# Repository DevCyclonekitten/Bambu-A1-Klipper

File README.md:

# Bambu-A1-Klipper
 A repository about the development of modifying a bambu labs a1 printer to run on klipper

Site viewable at: https://devcyclonekitten.github.io/Bambu-A1-Klipper/

Uhh this hasn't been updated, but so far I did get the printer working, then killed mainboard
I have all components working, except screen and eddy current sensor, am just finalizing pcb's then trying to rebuild.

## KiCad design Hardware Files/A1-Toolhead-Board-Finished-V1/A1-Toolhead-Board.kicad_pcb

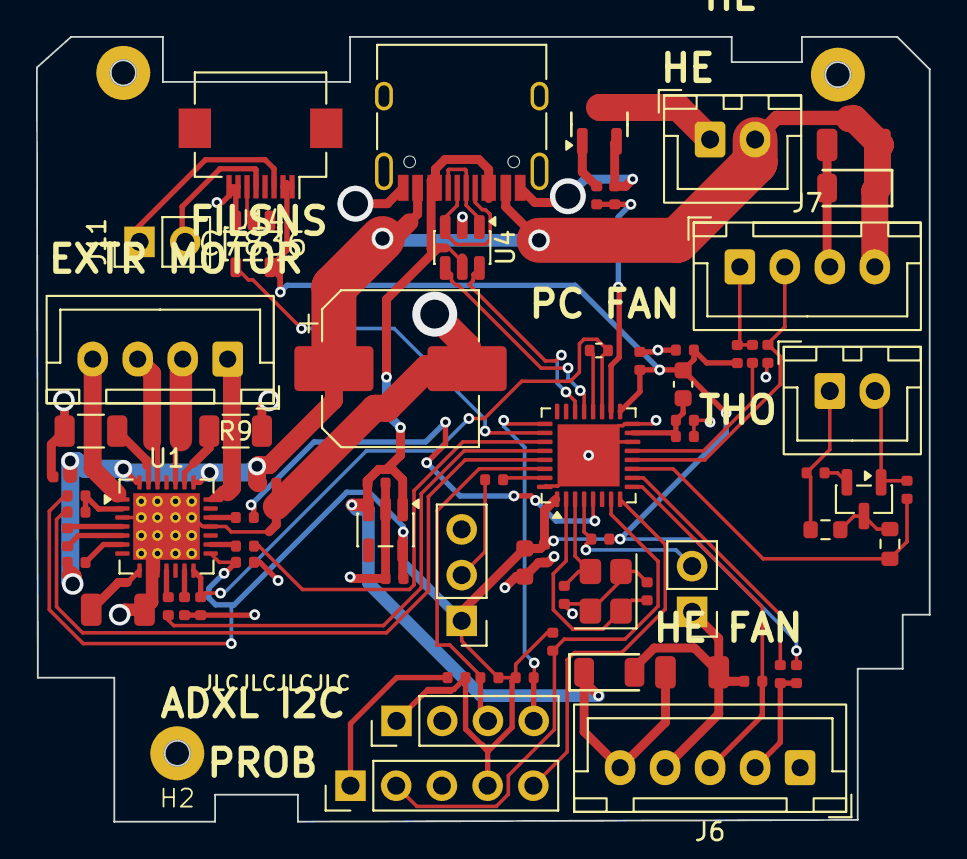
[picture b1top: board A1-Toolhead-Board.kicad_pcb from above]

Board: 2 copper layers, 49.6 x 43.6 mm, 74 parts (0 on the bottom side), 56 nets.

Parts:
C1, C3, C4, C5, C8, C13, C16: 100nF; C_0402
C2: 100uF 50V; CP_Elec_8x10.5
C6: 22nF; C_0402
C7, C11, C12: 4.7uF; C_1206
C9, C17, C18, C21, C24: 1uF; C_0402
C19: 10uF; C_0603
C20: 10nF; C_0402
C22, C23: 30pF; C_0402
D1, D4: DSK26; D_SOD-123FL
D3: BAV99; SOT-23
FB1: 120r 100MHz; C_0603_1608Metric
H1, H2, H3: m1.5; MountingHole_M1.5
J1: Motor_E; JST_XH_B4B-XH-A_1x04_P2.50mm_Vertical
J2: BOOT; PinHeader_1x03_P2.54mm_Vertical
J6: EXF; JST_XH_B5B-XH-A_1x05_P2.50mm_Vertical
J7: PCF; JST_XH_B4B-XH-A_1x04_P2.50mm_Vertical
J9: ADXL345; PinHeader_1x04_P2.54mm_Vertical
J10: BL_PROBE; PinHeader_1x05_P2.54mm_Vertical
J11: EXTR_FIL; PinHeader_1x02_P2.54mm_Vertical
J12: THO; JST_XH_B2B-XH-A_1x02_P2.50mm_Vertical
J13: HE; JST_XH_B2B-XH-A_1x02_P2.50mm_Vertical
J14: FPC_FILAMENT_SENSOR; Hirose_FH12-8S-0.5SH_1x08-1MP_P0.50mm_Horizontal
P1: USB_C_Plug; USB_C_Receptacle_HRO_TYPE-C-31-M-12
PN1: Part_Num_JLCPCB
Q2: AO3400A; Q_SOT-23
R1: 1ko; R_0402_1005Metric
R2, R5, R8: 20kΩ; R_0402
R3, R4, R6, R21: 100Ω; R_0402
R7, R11, R19, R20, R24, R25, R28, R30: 10kΩ; R_0402
R9, R100: 100mO; R_1206_3216Metric
R16, R23, R26, R29, R31: 4.7kΩ; R_0402
R17, R18: 2.2kΩ; R_0603_1608Metric
R27: 10Ω; R_0402
SW1: SW_SPST; PinHeader_1x02_P2.54mm_Vertical
U1: TMC2209-LA; TMC2209-LargerVias
U2: STM32G431KBU3; QFN-32-1EP_5x5mm_P0.5mm_EP3.45x3.45mm
U4: USBLC6-2SC6; SOT-23-6
U5: TLV75733PDBV; SOT-23-5
U6: 74LVC1G17; SOT-23-5_L3.0-W1.7-P0.95-LS2.8-BR
Y1: Crystal_GND24; Crystal_SMD_3225-4Pin_3.2x2.5mm

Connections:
+3.3VADC: D3.2 (A), R16.1
+3V3: C8.1, C9.2, C13.1, C16.1, C17.1, C19.1, C21.1, FB1.2, J2.1, J9.1, J10.4, J14.1, J14.2, R5.2, R11.1, R19.2, R24.2, R26.2, R28.1, R29.2, U1.15 (VCC_IO), U2.1 (VDD), U2.17 (VDD), U5.5 (OUT), U6.5 (VCC)
+3V3A: C18.1, C20.1, FB1.1, U2.15 (VDDA)
+5V: C7.1, U1.8 (5VOUT)
+24V: C2.1, C3.1, C4.1, C5.2, C12.1, D1.1, J7.4, J13.2, P1.A4 (VBUS), P1.A9 (VBUS), P1.B4 (VBUS), P1.B9 (VBUS), U1.22 (VS), U1.28 (VS)
/communications/USB_D+: U2.22 (PA12), U4.6 (I/O1)
/communications/USB_D-: U2.21 (PA11), U4.4 (I/O2)
/communications/USB_PORT_D+: P1.A6 (D+), P1.B6 (D+), U4.1 (I/O1)
/communications/USB_PORT_D-: P1.A7 (D-), P1.B7 (D-), U4.3 (I/O2)
/fans/EXTR_FAN_PWM: J6.3, R23.1, U2.9 (PA4)
/fans/EXTR_FAN_TACH: R20.1, U2.10 (PA5)
/fans/PART_FAN_PWM: J7.2, R31.1, U2.12 (PA7)
/fans/PART_FAN_TACH: R25.1, U2.13 (PB0)
/heaters/HOTEND_PWM: R27.2, R30.2, U2.18 (PA8)
/heaters/THERMISTER: C1.1, R17.1, U2.11 (PA6)
/mcu/ADXL_SCK: J9.4, R26.1, U2.25 (PA15)
/mcu/ADXL_SDA: J9.3, R29.1, U2.30 (PB7)
/mcu/BIQU_BL_PROBE: J10.2, R28.2, U2.7 (PA2)
/mcu/BIQU_BL_SERVO: J10.5, U2.8 (PA3)
/mcu/EXTRUDER_DIAG: R21.1, U2.28 (PB5)
/mcu/EXTRUDER_DIR: R6.1, U2.5 (PA0)
/mcu/EXTRUDER_ENABLE: R3.1, U2.29 (PB6)
/mcu/EXTRUDER_RX: R1.1, U2.20 (PA10)
/mcu/EXTRUDER_STEP: R4.2, U2.27 (PB4)
/mcu/EXTRUDER_TX: R1.2, R2.2, U1.14 (~PD_UART), U2.19 (PA9)
/mcu/FILAMENT_SENSOR: U2.26 (PB3), U6.4
/reversed_filament_sensor/SNS1: J11.1, J14.3
/reversed_filament_sensor/SNS2: J11.2, J14.5
/reversed_filament_sensor/SNS3: J14.6, U6.2
GND: C1.2, C2.2, C3.2, C4.2, C7.2, C8.2, C9.1, C11.2, C12.2, C13.2, C16.2, C17.2, C18.2, C19.2, C20.2, C21.2, C22.2, C23.2, C24.1, D1.2, D3.1 (K), D4.2, J2.3, J6.4, J7.3, J9.2, J10.1, J10.3, J12.2, J14.7, J14.8, P1.A1 (GND), P1.A12 (GND), P1.B1 (GND), P1.B12 (GND), Q2.2 (S), R2.1, R8.1, R9.2, R23.2, R30.1, R31.2, R100.2, SW1.1 (A), U1.3 (GND), U1.9 (MS1_AD0), U1.10 (MS2_AD1), U1.18 (GND), U1.29 (EXP), U2.14 (VSSA), U2.16 (VSS), U2.32 (VSS), U2.33 (VSS), U4.2 (GND), U5.2 (GND), U6.3 (GND), Y1.2, Y1.4
unnamed: D3.3 (K), R17.2, R18.1
unnamed: J1.1, U1.21 (OA2)
unnamed: J1.2, U1.24 (OA1)
unnamed: J1.3, U1.26 (OB1)
unnamed: J1.4, U1.1 (OB2)
unnamed: J2.2, R7.1
unnamed: J6.2, R19.1, R20.2
unnamed: J7.1, R24.1, R25.2
unnamed: J12.1, R16.2, R18.2
unnamed: J13.1, Q2.3 (D)
unnamed: Q2.1 (G), R27.1
unnamed: R11.2, SW1.2 (B), U2.4 (PG10)
unnamed: R9.1, U1.23 (BRA)
unnamed: R100.1, U1.27 (BRB)
unnamed: R8.2, U1.13 (CLK)
unnamed: C6.1, U1.5 (CPI)
unnamed: C6.2, U1.4 (CPO)
unnamed: R21.2, U1.11 (DIAG)
unnamed: R6.2, U1.19 (DIR)
unnamed: R4.1, U1.16 (STEP)
unnamed: C5.1, U1.6 (VCP)
unnamed: R3.2, R5.1, U1.2 (~EN)
unnamed: R7.2, U2.31 (PB8)
unnamed: C23.1, U2.2 (PF0), Y1.1
unnamed: C22.1, U2.3 (PF1), Y1.3
VBUS: C11.1, C24.2, D4.1, J6.5, P1.A5 (CC1), P1.A8 (SBU1), P1.B5 (CC2), P1.B8 (SBU2), U4.5 (VBUS), U5.1 (IN), U5.3 (EN)

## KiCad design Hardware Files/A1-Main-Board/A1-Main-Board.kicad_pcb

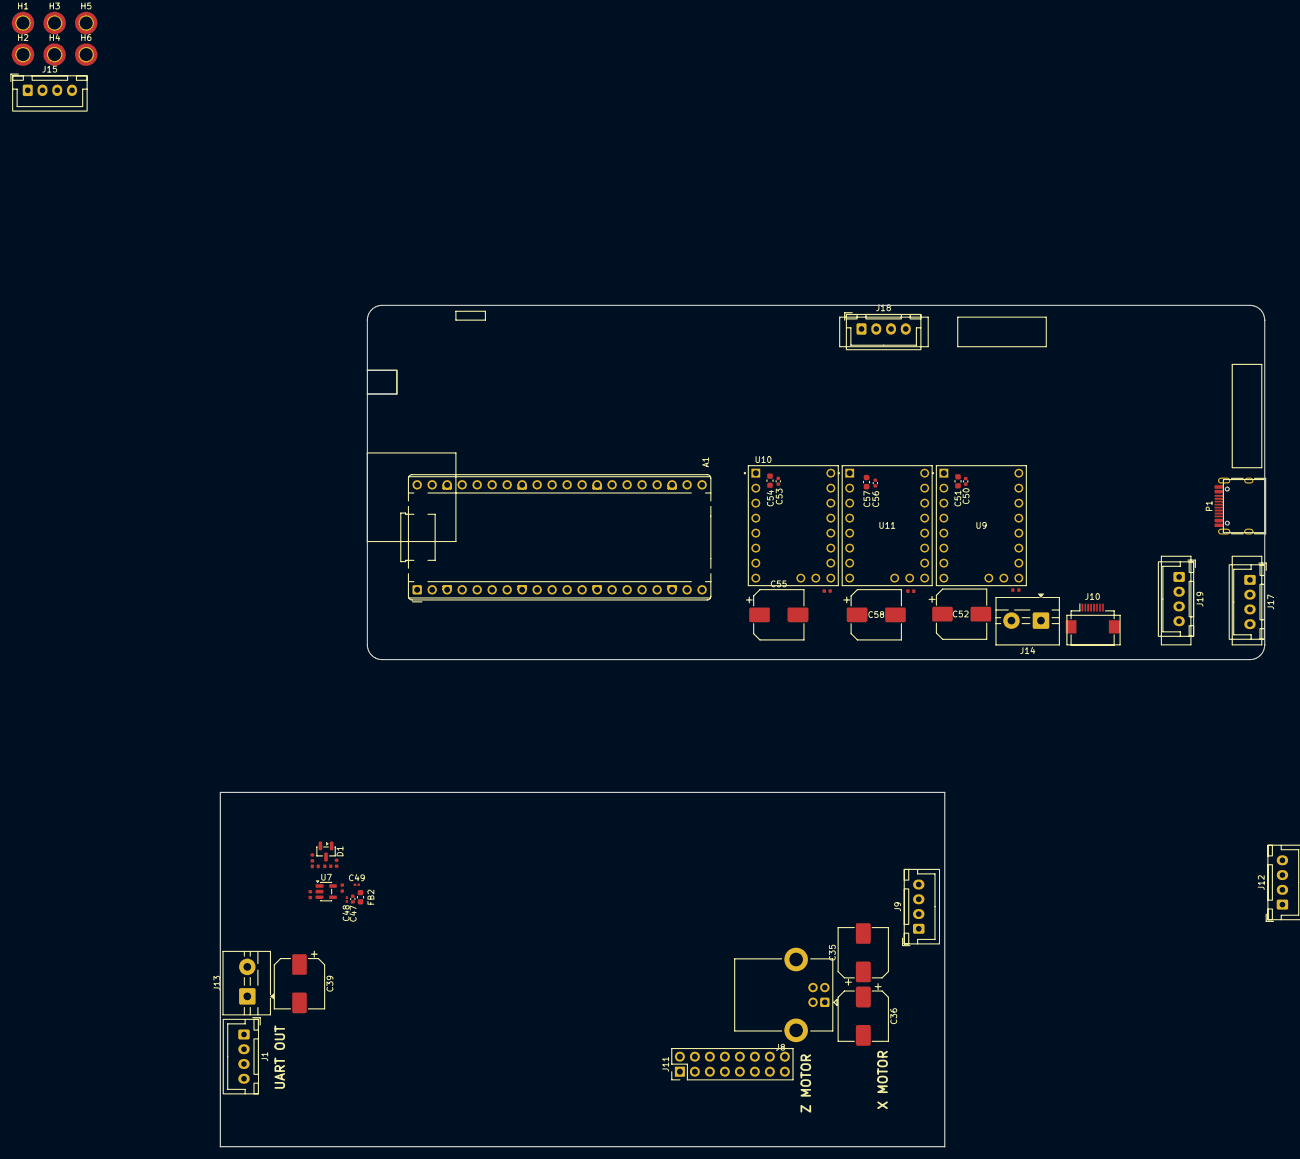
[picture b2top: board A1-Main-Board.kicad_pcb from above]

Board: 2 copper layers, 176.9 x 142.5 mm, 50 parts (0 on the bottom side), 38 nets, no tracks yet.

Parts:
A1: RaspberryPi_Pico; RaspberryPi_Pico_Common_THT
C35, C36, C39, C52, C55, C58: 100uF; CP_Elec_8x10
C42, C43: 1uF; C_0402
C47: 10nF; C_0402_1005Metric
C48, C49: 1uF; C_0201_0603Metric
C50, C53, C56: 100nF; C_0402_1005Metric
C51, C54, C57: 10uF; C_0603_1608Metric
C59: 100nF; C_0402
D1: BAV99; SOT-23
FB2: 120r 100MHz; C_0603_1608Metric
H1, H2, H3, H4, H5, H6: M1.5; MountingHole_2.2mm_M2_ISO14580_Pad_TopBottom
J1: MB_UART; JST_XH_B4B-XH-A_1x04_P2.50mm_Vertical
J8: USB_Toolhead_Outgoing; USB_B_Lumberg_2411_02_Horizontal
J9: Toolhead_USB; JST_XH_B4B-XH-A_1x04_P2.50mm_Vertical
J10: FPC_CON; Hirose_FH12-8S-0.5SH_1x08-1MP_P0.50mm_Horizontal
J11: Bed-Binder; PinHeader_2x08_P2.54mm_Vertical
J12: MotorJST; JST_XH_B4B-XH-A_1x04_P2.50mm_Vertical
J13, J14: Power-Input; TerminalBlock_MaiXu_MX126-5.0-02P_1x02_P5.00mm
J15: ExpansionPortJST; JST_XH_B4B-XH-A_1x04_P2.50mm_Vertical
J17, J18, J19: Motor Connector; JST_XH_B4B-XH-A_1x04_P2.50mm_Vertical
P1: USB_Toolhead_Incoming; USB_C_Receptacle_HRO_TYPE-C-31-M-12
R32, R33: 2.2kΩ; R_0402
R38, R39, R40: 10kΩ; R_0402
R41: 4.7kΩ; R_0402
U7: TLV75733PDBV; SOT-23-5
U9, U10, U11: TMC2209_SILENTSTEPSTICK; MODULE_TMC2209_SILENTSTEPSTICK

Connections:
+3V3: C43.1, C49.1, C50.1, C51.1, C53.1, C54.1, C56.1, C57.1, FB2.2, J1.4, R38.1, R39.1, R40.1, U7.5 (OUT), U9.2 (VIO), U10.2 (VIO), U10.15 (MS1), U11.2 (VIO)
+3V3A: A1.35 (ADC_VREF), C47.1, C48.1, D1.2 (A), FB2.1, R41.1
+5V: A1.39 (VSYS), C36.1, C39.1, J11.2, J13.2, P1.A5 (CC), P1.A8 (SBU1), P1.B5 (VCONN), P1.B8 (SBU2)
+24V: C35.1, C52.1, C55.1, C58.1, J14.2, P1.A4 (VBUS), P1.A9 (VBUS), P1.B4 (VBUS), P1.B9 (VBUS), U9.8 (VM), U10.8 (VM), U11.8 (VM)
/communications-toolhead/USB_D+: J8.3 (D+), J9.2, P1.A6 (D+)
/communications-toolhead/USB_D-: J8.2 (D-), J9.3, P1.A7 (D-)
/drivers/MA_DIAG: A1.7 (GPIO5), U9.18 (DIAG)
/drivers/MA_DIR: A1.6 (GPIO4), U9.9 (DIR)
/drivers/MA_ENABLE: A1.4 (GPIO2), R38.2, U9.16 (~EN)
/drivers/MA_STEP: A1.5 (GPIO3), U9.10 (STEP)
/drivers/MA_UART: A1.16 (GPIO12), U9.12 (UART), U10.12 (UART), U11.12 (UART)
/drivers/MB_DIAG: A1.12 (GPIO9), U10.18 (DIAG)
/drivers/MB_DIR: A1.11 (GPIO8), U10.9 (DIR)
/drivers/MB_ENABLE: A1.9 (GPIO6), R39.2, U10.16 (~EN)
/drivers/MB_STEP: A1.10 (GPIO7), U10.10 (STEP)
/drivers/MC_DIAG: A1.26 (GPIO20), U11.18 (DIAG)
/drivers/MC_DIR: A1.25 (GPIO19), U11.9 (DIR)
/drivers/MC_ENABLE: A1.22 (GPIO17), R40.2, U11.16 (~EN)
/drivers/MC_STEP: A1.24 (GPIO18), U11.10 (STEP)
/heated-bed/100k_THB_INP: J12.1, R33.1, R41.2
/heated-bed/BED_THERM_1: A1.31 (GPIO26_ADC0), C59.1, R32.2
/mcu-pico-tht/UART_RX: A1.2 (GPIO1), J1.2
/mcu-pico-tht/UART_TX: A1.1 (GPIO0), J1.3
GND: A1.3 (GND), A1.8 (GND), A1.13 (GND), A1.18 (GND), A1.23 (GND), A1.28 (GND), A1.33 (AGND), A1.38 (GND), C35.2, C36.2, C39.2, C42.1, C43.2, C47.2, C48.2, C49.2, C50.2, C51.2, C52.2, C53.2, C54.2, C55.2, C56.2, C57.2, C58.2, C59.2, D1.1 (K), J1.1, J8.4 (GND), J9.4, J11.6, J11.10, J11.14, J11.16, J12.2, J13.1, J14.1, P1.A1 (GND), P1.A12 (GND), P1.B1 (GND), P1.B12 (GND), U7.2 (GND), U9.1 (GND), U9.7 (GND), U9.14 (MS2), U9.15 (MS1), U10.1 (GND), U10.7 (GND), U10.14 (MS2), U11.1 (GND), U11.7 (GND), U11.15 (MS1)
unnamed: D1.3 (K), R32.1, R33.2
unnamed: J17.1, U9.5 (M2A)
unnamed: J17.2, U9.4 (M1A)
unnamed: J17.3, U9.3 (M1B)
unnamed: J17.4, U9.6 (M2B)
unnamed: J18.1, U10.5 (M2A)
unnamed: J18.2, U10.4 (M1A)
unnamed: J18.3, U10.3 (M1B)
unnamed: J18.4, U10.6 (M2B)
unnamed: J19.1, U11.5 (M2A)
unnamed: J19.2, U11.4 (M1A)
unnamed: J19.3, U11.3 (M1B)
unnamed: J19.4, U11.6 (M2B)
VBUS: C42.2, J8.1 (VBUS), J9.1, U7.1 (IN), U7.3 (EN)

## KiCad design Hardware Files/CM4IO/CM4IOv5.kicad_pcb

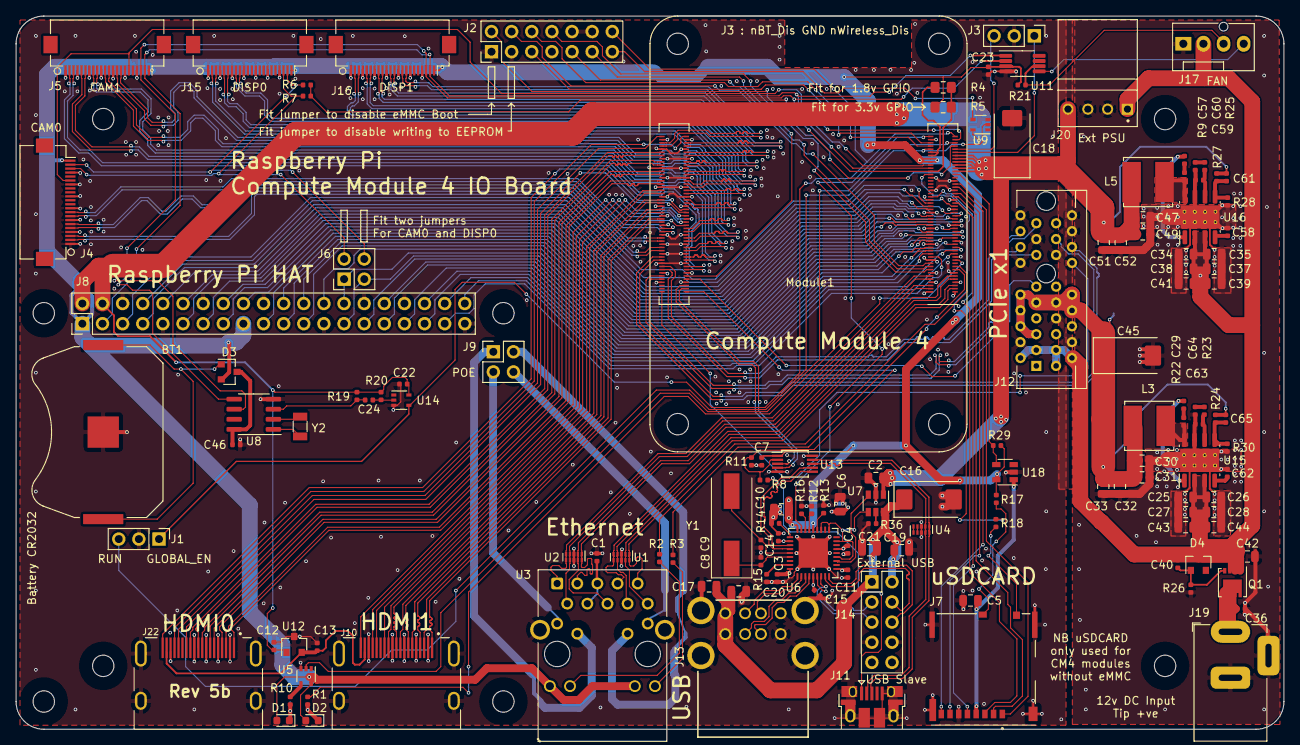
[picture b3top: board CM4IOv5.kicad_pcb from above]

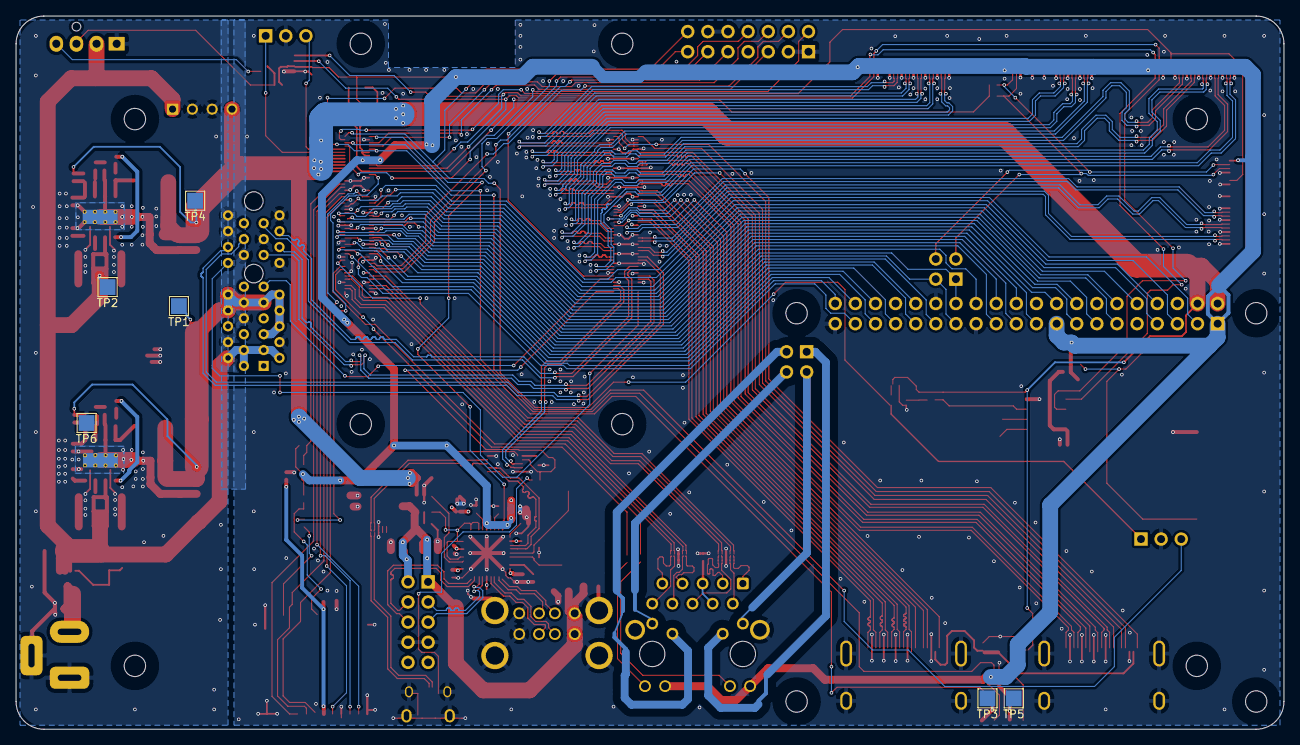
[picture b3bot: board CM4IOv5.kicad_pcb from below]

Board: 4 copper layers, 160.0 x 90.0 mm, 151 parts (6 on the bottom side), 204 nets.

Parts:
BT1: Battery_Cell; BatteryHolder_Keystone_3034_1x20mm
C1, C3, C4, C7, C11, C12, C13, C14, C15, C22, C23, C24, C29, C40, C46, C57, C58, C62: 100n; C_0402_1005Metric
C2, C5, C6, C10, C17, C19, C20, C21, C30, C31, C32, C33, C47, C49, C51, C52: 10u; C_0805_2012Metric
C8, C9: 27pF; C_0402_1005Metric
C16, C18, C45: 100uF; CP_EIA-7343-31_Kemet-D
C25, C26, C27, C28, C34, C35, C37, C38, C39, C41, C42, C43, C44: 10u 35v; C_0805_2012Metric
C36: 100n 100v; C_0402_1005Metric
C59, C61, C63, C65: nf; C_0402_1005Metric
C60, C64: 1.2nF; C_0402_1005Metric
D1: LED Red; LED_0603_1608Metric
D2: LED Green; LED_0603_1608Metric
D3: BAT54C-7-F; SOT-23
D4: MMBZ5242BLT3G; D_SOT-23_ANK
H1, H2, H3, H4, H5, H6, H7, H8: MountingHole; MountingHole_2.7mm_M2.5
J1, J3: Conn_01x03; PinHeader_1x03_P2.54mm_Vertical
J2: Conn_02x07_Odd_Even; PinHeader_2x07_P2.54mm_Vertical
J4, J5, J15, J16: Conn_01x22_Female; Hirose_FH12-22S-0.5SH_1x22-1MP_P0.50mm_Horizontal
J6, J9: THD-02-R; PinHeader_2x02_P2.54mm_Vertical
J7: Micro_SD_Card_Det; SDCARD_MOLEX_503398-1892
J8: THD-20-R; PinHeader_2x20_P2.54mm_Vertical
J10, J22: 690-019-298-412; EDAC 690-019-298-412
J11: USB_OTG; USB_Micro-B_EDAC_UCON00686
J12: 10018783-11200TLF; PCIex1-36
J13: 690-008-221-904; MOLEX_USB_67298-4090
J14: Conn_02x05_Odd_Even; PinHeader_2x05_P2.54mm_Vertical
J17: Molex 470531000; FanPinHeader_1x04_P2.54mm_Vertical
J19: Barrel_Jack; BarrelJack_Horizontal
J20: AMP171826-4; TE_171826-4
L3, L5: SRN6045TA-3R3Y; L_Bourns_SRN6045TA
Module1: ComputeModule4; Raspberry-Pi-4-Compute-Module
Q1: DMP3013SFV-7; Diodes_PowerDI3333-8
R1, R10: 1k; R_0402_1005Metric
R2, R3: 470R; R_0402_1005Metric
R4: nf; R_0805_2012Metric_Pad1.15x1.40mm_HandSolder
R5: 0R; R_0805_2012Metric_Pad1.15x1.40mm_HandSolder
R6, R7, R8, R11, R28: 2.2K 1%; R_0402_1005Metric
R9, R22: 10R; R_0402_1005Metric
R12, R13, R14, R16, R21: 36K 1%; R_0402_1005Metric
R15, R23, R26, R27, R29: 12K 1%; R_0402_1005Metric
R17, R18: nf; R_0402_1005Metric
R19, R20: 510K 1%; R_0402_1005Metric
R24: 47K 1%; R_0402_1005Metric
R25: 20K 1%; R_0402_1005Metric
R30, R36: 15K 1%; R_0402_1005Metric
TP1, TP2, TP3, TP4, TP5, TP6: TestPoint; TestPoint_Pad_2.0x2.0mm
U1, U2, U4: TPD4EUSB30; USON-10_2.5x1.0mm_P0.5mm
U3: MagJack-A70-112-331N126; TRJG0926HENL
U5, U9, U14: 74LVC1G07SE-7; SOT-353_SC-70-5
U6: USB2514B-I/M2; QFN-36-1EP_6x6mm_P0.5mm_EP3.7x3.7mm
U7: AP22653W6; SOT-23-6
U8: PCF85063AT/AAZ; SOIC-8_3.9x4.9mm_P1.27mm
U11: EMC2301-1-ACZL-TR; MSOP-8_3x3mm_P0.65mm
U12: RT9742SNGV; SOT-23
U13: FSUSB42MUX; MSOP-10_3x3mm_P0.5mm
U15, U16: AP64501SP-13; SOIC-8-1EP_3.9x4.9mm_P1.27mm_EP2.95x4.9mm_Mask2.71x3.4mm_Th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
U18: RT9742GGJ5; SOT-23-5
Y1: 24MHz; Crystal_SMD_HC49-SD
Y2: X32K768S301; Crystal_SMD_3215-2Pin_3.2x1.5mm

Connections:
/+3.3v: C3.1, C4.1, C6.1, C7.1, C10.1, C11.1, C14.1, C15.1, C23.1, D1.2 (A), D2.2 (A), D3.2, J4.22, J5.22, J8.1, J8.17, J15.22, J16.22, Module1.84 (+3.3v_(Output)), Module1.86 (+3.3v_(Output)), R5.1, R17.1, R21.2, R29.1, U3.15 (LEDG_A), U3.17 (LEDY_A), U5.5 (VCC), U6.5 (VDDA33), U6.10 (VDDA33), U6.15 (VDD33), U6.23 (VDD33), U6.27 (VBUS_DET), U6.29 (VDDA33), U6.36 (VDDA33), U11.3 (VDD), U13.1 (VCC), U18.5 (IN)
/+5v: C2.1, C12.1, C18.1, C22.1, C47.1, C49.1, C51.1, C52.1, C61.1, J8.2, J8.4, J20.4, L5.2, Module1.77 (+5v_(Input)), Module1.79 (+5v_(Input)), Module1.81 (+5v_(Input)), Module1.83 (+5v_(Input)), Module1.85 (+5v_(Input)), Module1.87 (+5v_(Input)), R19.2, R20.2, R27.1, TP4.1, U7.1 (IN), U9.5 (VCC), U12.1 (IN), U14.5 (VCC)
/+12v: C25.1, C26.1, C27.1, C28.1, C34.1, C35.1, C37.1, C38.1, C39.1, C40.1, C41.1, C42.1, C43.1, C44.1, D4.1 (K), J12.A2 (+12V), J12.A3 (+12V), J12.B1 (+12v), J12.B2 (+12v), J12.B3 (+12v), J17.2, J20.1, Q1.1 (S), Q1.2 (S), Q1.3 (S), TP2.1, U15.2 (VIN), U15.3 (EN), U16.2 (VIN), U16.3 (EN)
/CM4_GPIO ( Ethernet, GPIO, SDCARD)/+1.8v: Module1.88 (+1.8v_(Output)), Module1.90 (+1.8v_(Output)), R4.1
/CM4_GPIO ( Ethernet, GPIO, SDCARD)/AIN0: J2.5, Module1.96 (AnalogIP0)
/CM4_GPIO ( Ethernet, GPIO, SDCARD)/AIN1: J2.6, Module1.94 (AnalogIP1)
/CM4_GPIO ( Ethernet, GPIO, SDCARD)/BT_nDis: J3.3, Module1.91 (BT_nDisable)
/CM4_GPIO ( Ethernet, GPIO, SDCARD)/EEPROM_nWP: J2.4, Module1.20 (EEPROM_nWP)
/CM4_GPIO ( Ethernet, GPIO, SDCARD)/ETH_LEDG: Module1.17 (Ethernet_nLED2(3.3v)), R2.2
/CM4_GPIO ( Ethernet, GPIO, SDCARD)/ETH_LEDY: Module1.15 (Ethernet_nLED3(3.3v)), R3.2
/CM4_GPIO ( Ethernet, GPIO, SDCARD)/GLOBAL_EN: J1.1, J2.14, Module1.99 (Global_EN), U14.4
/CM4_GPIO ( Ethernet, GPIO, SDCARD)/GPIO2: J8.3, Module1.58 (GPIO2)
/CM4_GPIO ( Ethernet, GPIO, SDCARD)/GPIO3: J8.5, Module1.56 (GPIO3)
/CM4_GPIO ( Ethernet, GPIO, SDCARD)/GPIO4: J8.7, Module1.54 (GPIO4)
/CM4_GPIO ( Ethernet, GPIO, SDCARD)/GPIO5: J8.29, Module1.34 (GPIO5)
/CM4_GPIO ( Ethernet, GPIO, SDCARD)/GPIO6: J8.31, Module1.30 (GPIO6)
/CM4_GPIO ( Ethernet, GPIO, SDCARD)/GPIO7: J8.26, Module1.37 (GPIO7)
/CM4_GPIO ( Ethernet, GPIO, SDCARD)/GPIO8: J8.24, Module1.39 (GPIO8)
/CM4_GPIO ( Ethernet, GPIO, SDCARD)/GPIO9: J8.21, Module1.40 (GPIO9)
/CM4_GPIO ( Ethernet, GPIO, SDCARD)/GPIO10: J8.19, Module1.44 (GPIO10)
/CM4_GPIO ( Ethernet, GPIO, SDCARD)/GPIO11: J8.23, Module1.38 (GPIO11)
/CM4_GPIO ( Ethernet, GPIO, SDCARD)/GPIO12: J8.32, Module1.31 (GPIO12)
/CM4_GPIO ( Ethernet, GPIO, SDCARD)/GPIO13: J8.33, Module1.28 (GPIO13)
/CM4_GPIO ( Ethernet, GPIO, SDCARD)/GPIO14: J8.8, Module1.55 (GPIO14)
/CM4_GPIO ( Ethernet, GPIO, SDCARD)/GPIO15: J8.10, Module1.51 (GPIO15)
/CM4_GPIO ( Ethernet, GPIO, SDCARD)/GPIO16: J8.36, Module1.29 (GPIO16)
/CM4_GPIO ( Ethernet, GPIO, SDCARD)/GPIO17: J8.11, Module1.50 (GPIO17)
/CM4_GPIO ( Ethernet, GPIO, SDCARD)/GPIO18: J8.12, Module1.49 (GPIO18)
/CM4_GPIO ( Ethernet, GPIO, SDCARD)/GPIO19: J8.35, Module1.26 (GPIO19)
/CM4_GPIO ( Ethernet, GPIO, SDCARD)/GPIO20: J8.38, Module1.27 (GPIO20)
/CM4_GPIO ( Ethernet, GPIO, SDCARD)/GPIO21: J8.40, Module1.25 (GPIO21)
/CM4_GPIO ( Ethernet, GPIO, SDCARD)/GPIO22: J8.15, Module1.46 (GPIO22)
/CM4_GPIO ( Ethernet, GPIO, SDCARD)/GPIO23: J8.16, Module1.47 (GPIO23)
/CM4_GPIO ( Ethernet, GPIO, SDCARD)/GPIO24: J8.18, Module1.45 (GPIO24)
/CM4_GPIO ( Ethernet, GPIO, SDCARD)/GPIO25: J8.22, Module1.41 (GPIO25)
/CM4_GPIO ( Ethernet, GPIO, SDCARD)/GPIO26: J8.37, Module1.24 (GPIO26)
/CM4_GPIO ( Ethernet, GPIO, SDCARD)/GPIO27: J8.13, Module1.48 (GPIO27)
/CM4_GPIO ( Ethernet, GPIO, SDCARD)/GPIO_VREF: Module1.78 (GPIO_VREF(1.8v/3.3v_Input)), R4.2, R5.2, R6.1, R7.1
/CM4_GPIO ( Ethernet, GPIO, SDCARD)/ID_SC: J6.1, J8.28, Module1.35 (ID_SC)
/CM4_GPIO ( Ethernet, GPIO, SDCARD)/ID_SD: J6.3, J8.27, Module1.36 (ID_SD)
/CM4_GPIO ( Ethernet, GPIO, SDCARD)/RUN_PG: J1.3, Module1.92 (RUN_PG), U9.2
/CM4_GPIO ( Ethernet, GPIO, SDCARD)/Reserved: Module1.76 (Reserved), R18.1
/CM4_GPIO ( Ethernet, GPIO, SDCARD)/SD_CLK: J7.5 (CLK), Module1.57 (SD_CLK)
/CM4_GPIO ( Ethernet, GPIO, SDCARD)/SD_CMD: J7.3 (CMD), Module1.62 (SD_CMD)
/CM4_GPIO ( Ethernet, GPIO, SDCARD)/SD_DAT0: J7.7 (DAT0), Module1.63 (SD_DAT0)
/CM4_GPIO ( Ethernet, GPIO, SDCARD)/SD_DAT1: J7.8 (DAT1), Module1.67 (SD_DAT1)
/CM4_GPIO ( Ethernet, GPIO, SDCARD)/SD_DAT2: J7.1 (DAT2), Module1.69 (SD_DAT2)
/CM4_GPIO ( Ethernet, GPIO, SDCARD)/SD_DAT3: J7.2 (DAT3/CD), Module1.61 (SD_DAT3)
/CM4_GPIO ( Ethernet, GPIO, SDCARD)/SD_PWR: C5.1, J7.4 (VDD), U18.1 (OUT)
/CM4_GPIO ( Ethernet, GPIO, SDCARD)/SD_PWR_ON: Module1.75 (SD_PWR_ON), R29.2, U18.4 (EN)
/CM4_GPIO ( Ethernet, GPIO, SDCARD)/SYNC_IN: J2.8, Module1.16 (Ethernet_SYNC_IN(1.8v))
/CM4_GPIO ( Ethernet, GPIO, SDCARD)/SYNC_OUT: J2.9, Module1.18 (Ethernet_SYNC_OUT(1.8v))
/CM4_GPIO ( Ethernet, GPIO, SDCARD)/TR0_TAP: J9.3, U3.11 (VC1)
/CM4_GPIO ( Ethernet, GPIO, SDCARD)/TR1_TAP: J9.1, U3.12 (VC2)
/CM4_GPIO ( Ethernet, GPIO, SDCARD)/TR2_TAP: J9.2, U3.13 (VC3)
/CM4_GPIO ( Ethernet, GPIO, SDCARD)/TR3_TAP: J9.4, U3.14 (VC4)
/CM4_GPIO ( Ethernet, GPIO, SDCARD)/TRD0_N: Module1.10 (Ethernet_Pair0_N), U2.4 (D2+), U2.7, U3.2 (TRD0-)
/CM4_GPIO ( Ethernet, GPIO, SDCARD)/TRD0_P: Module1.12 (Ethernet_Pair0_P), U2.5 (D2-), U2.6, U3.1 (TRD0+)
/CM4_GPIO ( Ethernet, GPIO, SDCARD)/TRD1_N: Module1.6 (Ethernet_Pair1_N), U2.2 (D1-), U2.9, U3.6 (TRD1-)
/CM4_GPIO ( Ethernet, GPIO, SDCARD)/TRD1_P: Module1.4 (Ethernet_Pair1_P), U2.1 (D1+), U2.10, U3.3 (TRD1+)
/CM4_GPIO ( Ethernet, GPIO, SDCARD)/TRD2_N: Module1.9 (Ethernet_Pair2_N), U1.4 (D2+), U1.7, U3.8 (TRD2-)
/CM4_GPIO ( Ethernet, GPIO, SDCARD)/TRD2_P: Module1.11 (Ethernet_Pair2_P), U1.5 (D2-), U1.6, U3.7 (TRD2+)
/CM4_GPIO ( Ethernet, GPIO, SDCARD)/TRD3_N: Module1.5 (Ethernet_Pair3_N), U1.2 (D1-), U1.9, U3.10 (TRD3-)
/CM4_GPIO ( Ethernet, GPIO, SDCARD)/TRD3_P: Module1.3 (Ethernet_Pair3_P), U1.1 (D1+), U1.10, U3.9 (TRD3+)
/CM4_GPIO ( Ethernet, GPIO, SDCARD)/TV_OUT: J2.11, Module1.111 (VDAC_COMP)
/CM4_GPIO ( Ethernet, GPIO, SDCARD)/WL_nDis: J3.1, Module1.89 (WL_nDisable)
/CM4_GPIO ( Ethernet, GPIO, SDCARD)/nPWR_LED: Module1.95 (nPI_LED_PWR), U5.2
/CM4_GPIO ( Ethernet, GPIO, SDCARD)/nRPIBOOT: J2.2, Module1.93 (nRPIBOOT)
/CM4_HighSpeed/CAM0_C_N: J4.8, Module1.140 (CAM0_C_N)
/CM4_HighSpeed/CAM0_C_P: J4.9, Module1.142 (CAM0_C_P)
/CM4_HighSpeed/CAM0_D0_N: J4.2, Module1.128 (CAM0_D0_N)
/CM4_HighSpeed/CAM0_D0_P: J4.3, Module1.130 (CAM0_D0_P)
/CM4_HighSpeed/CAM0_D1_N: J4.5, Module1.134 (CAM0_D1_N)
/CM4_HighSpeed/CAM0_D1_P: J4.6, Module1.136 (CAM0_D1_P)
/CM4_HighSpeed/CAM1_C_N: J5.8, Module1.127 (CAM1_C_N)
/CM4_HighSpeed/CAM1_C_P: J5.9, Module1.129 (CAM1_C_P)
/CM4_HighSpeed/CAM1_D0_N: J5.2, Module1.115 (CAM1_D0_N)
/CM4_HighSpeed/CAM1_D0_P: J5.3, Module1.117 (CAM1_D0_P)
/CM4_HighSpeed/CAM1_D1_N: J5.5, Module1.121 (CAM1_D1_N)
/CM4_HighSpeed/CAM1_D1_P: J5.6, Module1.123 (CAM1_D1_P)
/CM4_HighSpeed/CAM1_D2_N: J5.11, Module1.133 (CAM1_D2_N)
/CM4_HighSpeed/CAM1_D2_P: J5.12, Module1.135 (CAM1_D2_P)
/CM4_HighSpeed/CAM1_D3_N: J5.14, Module1.139 (CAM1_D3_N)
/CM4_HighSpeed/CAM1_D3_P: J5.15, Module1.141 (CAM1_D3_P)
/CM4_HighSpeed/CAM_GPIO: J4.17, J5.17, Module1.97 (Camera_GPIO)
/CM4_HighSpeed/DSI0_C_N: J15.8, Module1.169 (DSI0_C_N)
/CM4_HighSpeed/DSI0_C_P: J15.9, Module1.171 (DSI0_C_P)
/CM4_HighSpeed/DSI0_D0_N: J15.2, Module1.157 (DSI0_D0_N)
/CM4_HighSpeed/DSI0_D0_P: J15.3, Module1.159 (DSI0_D0_P)
/CM4_HighSpeed/DSI0_D1_N: J15.5, Module1.163 (DSI0_D1_N)
/CM4_HighSpeed/DSI0_D1_P: J15.6, Module1.165 (DSI0_D1_P)
/CM4_HighSpeed/DSI1_C_N: J16.8, Module1.187 (DSI1_C_N)
/CM4_HighSpeed/DSI1_C_P: J16.9, Module1.189 (DSI1_C_P)
/CM4_HighSpeed/DSI1_D0_N: J16.2, Module1.175 (DSI1_D0_N)
/CM4_HighSpeed/DSI1_D0_P: J16.3, Module1.177 (DSI1_D0_P)
/CM4_HighSpeed/DSI1_D1_N: J16.5, Module1.181 (DSI1_D1_N)
/CM4_HighSpeed/DSI1_D1_P: J16.6, Module1.183 (DSI1_D1_P)
/CM4_HighSpeed/DSI1_D2_N: J16.11, Module1.193 (DSI1_D2_N)
/CM4_HighSpeed/DSI1_D2_P: J16.12, Module1.195 (DSI1_D2_P)
/CM4_HighSpeed/DSI1_D3_N: J16.14, Module1.194 (DSI1_D3_N)
/CM4_HighSpeed/DSI1_D3_P: J16.15, Module1.196 (DSI1_D3_P)
/CM4_HighSpeed/HDMI0_CEC: J22.13 (CEC), Module1.151 (HDMI0_CEC)
/CM4_HighSpeed/HDMI0_CK_N: J22.12 (CK-), Module1.190 (HDMI0_CLK_N)
/CM4_HighSpeed/HDMI0_CK_P: J22.10 (CK+), Module1.188 (HDMI0_CLK_P)
/CM4_HighSpeed/HDMI0_D0_N: J22.9 (D0-), Module1.184 (HDMI0_TX0_N)
/CM4_HighSpeed/HDMI0_D0_P: J22.7 (D0+), Module1.182 (HDMI0_TX0_P)
/CM4_HighSpeed/HDMI0_D1_N: J22.6 (D1-), Module1.178 (HDMI0_TX1_N)
/CM4_HighSpeed/HDMI0_D1_P: J22.4 (D1+), Module1.176 (HDMI0_TX1_P)
/CM4_HighSpeed/HDMI0_D2_N: J22.3 (D2-), Module1.172 (HDMI0_TX2_N)
/CM4_HighSpeed/HDMI0_D2_P: J22.1 (D2+), Module1.170 (HDMI0_TX2_P)
/CM4_HighSpeed/HDMI0_HOTPLUG: J22.19 (HPD/HEAC-), Module1.153 (HDMI0_HOTPLUG)
/CM4_HighSpeed/HDMI0_SCL: J22.15 (SCL), Module1.200 (HDMI0_SCL)
/CM4_HighSpeed/HDMI0_SDA: J22.16 (SDA), Module1.199 (HDMI0_SDA)
/CM4_HighSpeed/HDMI1_CEC: J10.13 (CEC), Module1.149 (HDMI1_CEC)
/CM4_HighSpeed/HDMI1_CK_N: J10.12 (CK-), Module1.166 (HDMI1_CLK_N)
/CM4_HighSpeed/HDMI1_CK_P: J10.10 (CK+), Module1.164 (HDMI1_CLK_P)
/CM4_HighSpeed/HDMI1_D0_N: J10.9 (D0-), Module1.160 (HDMI1_TX0_N)
/CM4_HighSpeed/HDMI1_D0_P: J10.7 (D0+), Module1.158 (HDMI1_TX0_P)
/CM4_HighSpeed/HDMI1_D1_N: J10.6 (D1-), Module1.154 (HDMI1_TX1_N)
/CM4_HighSpeed/HDMI1_D1_P: J10.4 (D1+), Module1.152 (HDMI1_TX1_P)
/CM4_HighSpeed/HDMI1_D2_N: J10.3 (D2-), Module1.148 (HDMI1_TX2_N)
/CM4_HighSpeed/HDMI1_D2_P: J10.1 (D2+), Module1.146 (HDMI1_TX2_P)
/CM4_HighSpeed/HDMI1_HOTPLUG: J10.19 (HPD/HEAC-), Module1.143 (HDMI1_HOTPLUG)
/CM4_HighSpeed/HDMI1_SCL: J10.15 (SCL), Module1.147 (HDMI1_SCL)
/CM4_HighSpeed/HDMI1_SDA: J10.16 (SDA), Module1.145 (HDMI1_SDA)
/CM4_HighSpeed/HDMI_5v: C13.1, J10.18 (+5V), J22.18 (+5V), U12.2 (OUT)
/CM4_HighSpeed/PCIE_CLK_N: J12.A14 (REFCLK-), Module1.112 (PCIe_CLK_N)
/CM4_HighSpeed/PCIE_CLK_P: J12.A13 (REFCLK+), Module1.110 (PCIe_CLK_P)
/CM4_HighSpeed/PCIE_CLK_nREQ: J12.B12 (nCLKREQ), Module1.102 (PCIe_CLK_nREQ)
/CM4_HighSpeed/PCIE_RX_N: J12.A16 (PERP0), Module1.118 (PCIe_RX_N)
/CM4_HighSpeed/PCIE_RX_P: J12.A17 (PERN0), Module1.116 (PCIe_RX_P)
/CM4_HighSpeed/PCIE_TX_N: J12.B14 (PETP0), Module1.124 (PCIe_TX_N)
/CM4_HighSpeed/PCIE_TX_P: J12.B15 (PETN0), Module1.122 (PCIe_TX_P)
/CM4_HighSpeed/PCIE_nRST: J12.A11 (nPERST), Module1.109 (PCIe_nRST)
/CM4_HighSpeed/SCL0: J5.20, J16.20, Module1.80 (SCL0), U8.6 (SCL), U11.2 (SCL)
/CM4_HighSpeed/SCL1: J4.20, J6.2, J15.20, R7.2
/CM4_HighSpeed/SDA0: J5.21, J16.21, Module1.82 (SDA0), U8.5 (SDA), U11.1 (SDA)
/CM4_HighSpeed/SDA1: J4.21, J6.4, J15.21, R6.2
/CM4_HighSpeed/USB2_N: Module1.103 (USB2_N), U13.4 (D_N)
/CM4_HighSpeed/USB2_P: Module1.105 (USB2_P), U13.3 (D_P)
/CM4_HighSpeed/USBOTG_ID: Module1.101 (USB_OTG_ID), R8.2, R11.1, U13.2 (SEL)
/PCIe-connector/+3.3v: C30.1, C31.1, C32.1, C33.1, C45.1, C65.1, J12.A5 (TCK), J12.A6 (TDI), J12.A8 (TMS), J12.A9 (+3.3V), J12.A10 (+3.3V), J12.B8 (+3.3v), J12.B9 (nTRST), J12.B10 (+3.3vAUX), L3.2, R24.1, TP1.1
/RTC , Wakeup, FAN/nRTC_INT: C24.2, R19.1, U8.3 (~INT)
/USB2-HUB/HD1_N: J13.2 (D-`), U6.1 (USBDM_DN1/PRT_DIS_M1)
/USB2-HUB/HD1_P: J13.3 (D+`), U6.2 (USBDP_DN1/PRT_DIS_P1)
/USB2-HUB/HD2_N: J13.6 (D-), U6.3 (USBDM_DN2/PRT_DIS_M2)
/USB2-HUB/HD2_P: J13.7 (D+), U6.4 (USBDP_DN2/PRT_DIS_P2)
/USB2-HUB/HD3_N: J14.3, U6.6 (USBDM_DN3/PRT_DIS_M3)
/USB2-HUB/HD3_P: J14.5, U6.7 (USBDP_DN3/PRT_DIS_P3)
/USB2-HUB/HD4_N: J14.4, U6.8 (USBDM_DN4/PRT_DIS_M4)
/USB2-HUB/HD4_P: J14.6, U6.9 (USBDP_DN4/PRT_DIS_P4)
/USB2-HUB/PWR1: U6.12 (PRTPWR1/BC_EN1), U7.3 (EN)
/USB2-HUB/USBD_N: J11.2 (D-), U4.4 (D2+), U4.7, U13.8 (HSD1_M)
/USB2-HUB/USBD_P: J11.3 (D+), U4.5 (D2-), U4.6, U13.9 (HSD1_P)
/USB2-HUB/USBH_N: U6.30 (USBDM_UP), U13.6 (HSD0_M)
/USB2-HUB/USBH_P: U6.31 (USBDP_UP), U13.7 (HSD0_P)
/USB2-HUB/VBUS: C16.1, C17.1, C19.1, C20.1, C21.1, J13.1 (VBUS`), J13.5 (VBUS), J14.1, J14.2, U7.6 (OUT)
/USB2-HUB/nOCS1: U6.13 (OCS_N1), U6.17 (OCS_N2), U6.19 (OCS_N3), U6.21 (OCS_N4), U7.4 (nFault)
/nEXTRST: Module1.100 (nEXTRST), U6.26 (RESET_N)
GND: BT1.2 (-), C1.2, C2.2, C3.2, C4.2, C5.2, C6.2, C7.2, C8.2, C9.2, C10.2, C11.2, C12.2, C13.2, C14.2, C15.2, C16.2, C17.2, C18.2, C19.2, C20.2, C21.2, C22.2, C23.2, C25.2, C26.2, C27.2, C28.2, C30.2, C31.2, C32.2, C33.2, C34.2, C35.2, C36.2, C37.2, C38.2, C39.2, C41.2, C42.2, C43.2, C44.2, C45.2, C46.2, C47.2, C49.2, C51.2, C52.2, C58.2, C59.2, C60.2, C62.2, C63.2, C64.2, J1.2, J2.1, J2.3, J2.7, J2.10, J2.12, J3.2, J4.1, J4.4, J4.7, J4.10, J4.13, J4.16, J4.19, J5.1, J5.4, J5.7, J5.10, J5.13, J5.16, J5.19, J7.6 (VSS), J7.11 (SHIELD), J8.6, J8.9, J8.14, J8.20, J8.25, J8.30, J8.34, J8.39, J10.2 (D2S), J10.5 (D1S), J10.8 (D0S), J10.11 (CKS), J10.17 (GND), J10.SH1 (SH), J10.SH2 (SH), J10.SH3 (SH), J10.SH4 (SH), J11.5 (GND), J11.6 (Shield), J12.A4 (GND), J12.A12 (GND), J12.A15 (GND), J12.A18 (GND), J12.B4 (GND), J12.B7 (GND), J12.B13 (GND), J12.B16 (GND), J12.B18 (GND), J13.4 (GND`), J13.8 (GND), J13.MT1, J13.MT2, J13.MT3, J13.MT4, J14.7, J14.8, J15.1, J15.4, J15.7, J15.10, J15.13, J15.16, J15.19, J16.1, J16.4, J16.7, J16.10, J16.13, J16.16, J16.19, J17.1, J19.2, J19.3, J20.2, J20.3, J22.2 (D2S), J22.5 (D1S), J22.8 (D0S), J22.11 (CKS), J22.17 (GND), J22.SH1 (SH), J22.SH2 (SH), J22.SH3 (SH), J22.SH4 (SH), Module1.1 (GND), Module1.2 (GND), Module1.7 (GND), Module1.8 (GND), Module1.13 (GND), Module1.14 (GND), Module1.22 (GND), Module1.23 (GND), Module1.32 (GND), Module1.33 (GND), Module1.42 (GND), Module1.43 (GND), Module1.52 (GND), Module1.53 (GND), Module1.59 (GND), Module1.60 (GND), Module1.65 (GND), Module1.66 (GND), Module1.71 (GND), Module1.74 (GND), Module1.98 (GND), Module1.107 (GND), Module1.108 (GND), Module1.113 (GND), Module1.114 (GND), Module1.119 (GND), Module1.120 (GND), Module1.125 (GND), Module1.126 (GND), Module1.131 (GND), Module1.132 (GND), Module1.137 (GND), Module1.138 (GND), Module1.144 (GND), Module1.150 (GND), Module1.155 (GND), Module1.156 (GND), Module1.161 (GND), Module1.162 (GND), Module1.167 (GND), Module1.168 (GND), Module1.173 (GND), Module1.174 (GND), Module1.179 (GND), Module1.180 (GND), Module1.185 (GND), Module1.186 (GND), Module1.191 (GND), Module1.192 (GND), Module1.197 (GND), Module1.198 (GND), R11.2, R12.2, R13.2, R14.2, R15.1, R16.2, R26.2, R28.2, R30.2, R36.2, TP6.1, U1.3 (GND), U1.8 (GND), U2.3 (GND), U2.8 (GND), U3.19 (SHIELD), U3.20 (SHIELD), U4.3 (GND), U4.8 (GND), U5.3 (GND), U6.37 (VSS), U7.2 (GND), U8.4 (VSS), U9.3 (GND), U11.4 (GND), U12.3 (GND), U13.5 (GND), U13.10 (nOE), U14.3 (GND), U15.7 (GND), U15.9 (EP), U16.7 (GND), U16.9 (EP), U18.2 (GND)
unnamed: BT1.1 (+), D3.1
unnamed: C1.1, U3.4 (CT), U3.5 (CT)
unnamed: C8.1, U6.33 (XTALIN/CLKIN), Y1.1
unnamed: C9.1, U6.32 (XTALOUT), Y1.2
unnamed: C24.1, R20.1, U14.2
unnamed: C29.1, R22.2
unnamed: C29.2, U15.1 (BST)
unnamed: C36.1, J19.1, Q1.5 (D)
unnamed: C40.2, D4.2 (A), Q1.4 (G), R26.1
unnamed: C46.1, D3.3, U8.8 (VDD)
unnamed: C57.1, R9.2
unnamed: C57.2, U16.1 (BST)
unnamed: C58.1, U16.4 (SS)
unnamed: C59.1, R25.1, U16.6 (COMP)
unnamed: C60.1, R25.2
unnamed: C61.2, R27.2, R28.1, U16.5 (FB)
unnamed: C62.1, U15.4 (SS)
unnamed: C63.1, R23.1, U15.6 (COMP)
unnamed: C64.1, R23.2
unnamed: C65.2, R24.2, R30.1, U15.5 (FB)
unnamed: D1.1 (K), R10.1, TP5.1
unnamed: D2.1 (K), R1.1, TP3.1
unnamed: J2.13, U9.4
unnamed: J7.9 (DET_B), R18.2
unnamed: J7.10 (DET_A), R17.2
unnamed: J11.1 (VBUS), R8.1
unnamed: J17.3, R21.1, U11.6 (TACH)
unnamed: J17.4, U11.5 (PWM)
unnamed: L3.1, R22.1, U15.8 (SW)
unnamed: L5.1, R9.1, U16.8 (SW)
unnamed: Module1.21 (PI_nLED_Activity), R1.2
unnamed: R2.1, U3.16 (LEDG_K)
unnamed: R3.1, U3.18 (LEDY_K)
unnamed: R10.2, U5.4
unnamed: R12.1, U6.24 (SCL/SMBCLK/CFG_SEL0)
unnamed: R13.1, U6.22 (SDA/SMBDATA/NON_REM1)
unnamed: R14.1, U6.28 (SUSP_IND/LOCAL_PWR/NON_REM0)
unnamed: R15.2, U6.35 (RBIAS)
unnamed: R16.1, U6.25 (HS_IND/CFG_SEL1)
unnamed: R36.1, U7.5 (ILIM)
unnamed: U4.1 (D1+), U4.10
unnamed: U4.2 (D1-), U4.9
unnamed: U8.1 (OSCI), Y2.2
unnamed: U8.2 (OSCO), Y2.1

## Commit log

2025-12-22 e
    e
2025-12-22 Create jekyll-gh-pages.yml
    Fixed it bc i am stupid
2025-12-22 Update jekyll-gh-pages.yml
    Reverted things bc me thinking im smart actually broke things.
2026-01-01 Bump just-the-docs from 0.10.1 to 0.10.2
    Bumps [just-the-docs](https://github.com/just-the-docs/just-the-docs) from 0.10.1 to 0.10.2.
    - [Release notes](https://github.com/just-the-docs/just-the-docs/releases)
    - [Changelog](https://github.com/just-the-docs/just-the-docs/blob/main/CHANGELOG.md)
    - [Commits](https://github.com/just-the-docs/just-the-docs/compare/v0.10.1...v0.10.2)
    ---
    updated-dependencies:
2026-01-02 Bump just-the-docs from 0.10.1 to 0.11.0
    Bumps [just-the-docs](https://github.com/just-the-docs/just-the-docs) from 0.10.1 to 0.11.0.
    - [Release notes](https://github.com/just-the-docs/just-the-docs/releases)
    - [Changelog](https://github.com/just-the-docs/just-the-docs/blob/main/CHANGELOG.md)
    - [Commits](https://github.com/just-the-docs/just-the-docs/compare/v0.10.1...v0.11.0)
    ---
    updated-dependencies:
2026-01-05 Bump just-the-docs from 0.10.1 to 0.11.1
    Bumps [just-the-docs](https://github.com/just-the-docs/just-the-docs) from 0.10.1 to 0.11.1.
    - [Release notes](https://github.com/just-the-docs/just-the-docs/releases)
    - [Changelog](https://github.com/just-the-docs/just-the-docs/blob/main/CHANGELOG.md)
    - [Commits](https://github.com/just-the-docs/just-the-docs/compare/v0.10.1...v0.11.1)
    ---
    updated-dependencies:
2026-01-06 Just chucked whatever is here
    Going on holidays and just have an old version but this is backup skibidi 67
2026-01-26 Bump just-the-docs from 0.10.1 to 0.12.0
    Bumps [just-the-docs](https://github.com/just-the-docs/just-the-docs) from 0.10.1 to 0.12.0.
    - [Release notes](https://github.com/just-the-docs/just-the-docs/releases)
    - [Changelog](https://github.com/just-the-docs/just-the-docs/blob/main/CHANGELOG.md)
    - [Commits](https://github.com/just-the-docs/just-the-docs/compare/v0.10.1...v0.12.0)
    ---
    updated-dependencies:
